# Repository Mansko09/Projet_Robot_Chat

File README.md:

# Projet Robot Chat

**ESE – Projet de groupe**

## Introduction

Dans le cadre de la spécialité de 3e année ESE à l'ENSEA, ce projet a pour objectif la conception complète d’un **robot mobile autonome à deux roues motrices**, destiné à participer à un jeu de type **chat et souris** face aux robots des autres groupes. Ce projet a été réalisé par Florian, David, Danilo et Mantou.
Au-delà de l’aspect ludique, ce projet mobilise des compétences variées en **électronique**, **mécanique** et **logiciel embarqué temps réel**, avec des contraintes fortes de sécurité (anti-chute), de réactivité et de robustesse matérielle.

Le robot, nommé **Félix**, doit être capable de se déplacer de manière autonome, de détecter son environnement, de réagir à des événements physiques (vide, chocs) et d’adapter dynamiquement son comportement.

---

## Objectifs fonctionnels

Pour atteindre ce comportement, plusieurs fonctions clés doivent être mises en place :

1. **Déplacement**

   * Roues + moteurs
   * Drivers de moteurs (PWM via timers)
   * Encodeurs (lecture via timers)

2. **Anti-chute**

   * Détection des bords avec capteur **ToF** (I²C)

3. **Détection des adversaires**

   * Capteur **LIDAR** pour repérer d’autres robots

4. **Détection de collisions**

   * Échange de rôles lors d’un choc (capteur **accéléromètre**)

5. **Communication**

   * Liaison **Bluetooth** (STM32WB55CEU6)

6. **Alimentation**

   * Batterie et gestion d’énergie (7.2 V → régulateurs 5 V & 3.3 V)

---

## Composants principaux

* **Microcontrôleur** : STM32WB55CEU6 (ARM Cortex-M4, BLE intégré)
* **Quartz** : 32 MHz 
* **Connecteur SWD/STLink** : (Farnell : 3226055)
* **Moteurs** : DFRobot FIT0520 ou FIT0521
* **Alimentation** : Batterie NiMH 7.2 V 1.3 Ah (RS : 777-0377)

  * Régulateur 5 V : MP1475DJ-LF-P
  * Régulateur 3.3 V : BU33SD5WG-TR
* **Drivers moteurs** : ZXBM5210 (un par roue)
* **Capteurs** :

  * LIDAR YDLIDAR X2
  * Accéléromètre ADXL343BCCZ-RL
  * Capteur ToF anti-chute
  * Multiplexeur : TCA9548A
* **Connecteurs** : JST 2.54 mm
* **Interface utilisateur** :

  * LED rouge/verte
  * Boutons poussoirs Wurth 430182070816 (6×6 mm, H9.5 mm)
  * Interrupteur ON/OFF Wurth 472121020311

---

## Conception réalisée

1. **Électronique**

   * Schéma électrique et PCB personnalisé
   * Routage, fabrication et soudure des composants

2. **Mécanique**

   * Conception du châssis sur **Onshape**
   * Intégration du PCB, moteurs, capteurs et batterie

3. **Logiciel embarqué**

   * Contrôle moteurs et capteurs

## Avancement du projet

* [x] Choix des composants et architecture générale
* [x] Schéma et routage PCB
* [x] Impression 3D du robot
* [x] Développement logiciel de base
* [ ] Intégration LIDAR et logique “chat/souris”

## Architecture générale 

## Structure du Code

### 1. Cerveau et Communication

Nous avons retenu le microcontrôleur **STM32WB55CEU6**, un choix motivé par des considérations de performance, de modularité et de fiabilité.

- **Mobilité et pilotage des drivers**  
  Chaque moteur est commandé par un driver piloté en PWM. Le logiciel intègre une gestion avancée des rampes de vitesse avec des profils asymétriques : accélération progressive et freinage brutal. Cette approche permet de préserver les moteurs tout en assurant un arrêt d’urgence immédiat lors de la détection de vide.  
  Les modes de freinage exploitent le **BRAKE_MODE** (court-circuit des moteurs) via le pont en H afin de garantir une immobilisation quasi instantanée sur les bords de table.

- **Intelligence embarquée et navigation**  
  Grâce à l’odométrie différentielle et aux encodeurs, la position $(x, y)$ ainsi que l’orientation $(\theta)$ du robot sont calculées en temps réel, permettant une navigation autonome précise.

- **Architecture logicielle sous FreeRTOS**  
  Le logiciel est structuré autour de plusieurs tâches concurrentes :
  - **Task_TOF** : mise à jour de la variable `vide` toutes les 20 ms, indiquant l’identifiant du capteur ToF détectant un vide ;
  - **Task_Motor** : gestion de l’odométrie et application des signaux PWM toutes les 10 ms ;
  - **Task_Control** : tâche décisionnelle principale, exécutée toutes les 20 ms, implémentant une machine à états finis (FSM) pilotant le comportement global du robot.

  **Rôle détaillé de la Task_Control**  
  La tâche **Task_Control** agit comme le véritable « cerveau » du robot. Elle fonctionne de manière asynchrone par rapport à la commande des moteurs et s’appuie sur une **Machine à États Finis (FSM)** pour orchestrer les actions de Félix en fonction des événements extérieurs.

  1. **Gestion de l’état global (Start / Stop)**  
     Avant toute logique de déplacement, la tâche surveille le flag `AccData`, mis à jour par l’accéléromètre via une interruption matérielle.  
     Un choc détecté agit comme un interrupteur logiciel (*toggle*) :
     - passage à l’état **Inactif** : LED rouge allumée, moteurs coupés ;
     - passage à l’état **Actif** : LED verte allumée, lancement de la mission.

  2. **Séquençage des déplacements (FSM)**  
     Lorsque le robot est actif, il suit un cycle comportemental conçu pour la survie et l’exploration :
     - **MOVE_FWD (marche avant)** : état par défaut. La tâche surveille en continu le registre `vide`. Dès qu’une bordure est détectée par un capteur ToF, une transition immédiate vers l’état de freinage est imposée.
     - **MOVE_BRAKE (sécurité)** : état intermédiaire déclenchant un arrêt d’urgence, voire une brève impulsion inverse, afin de compenser l’inertie et empêcher le dépassement du bord.
     - **MOVE_BACKWARD & MOVE_TURN** : une fois le robot immobilisé, une manœuvre de dégagement est engagée. Celle-ci est temporisée par `timer_state` et permet au robot de reculer, de modifier son orientation, puis de revenir automatiquement à l’état **MOVE_FWD**.

- **Perception sensorielle anti-chute**  
  Quatre capteurs **ToF VL53L0X** surveillent en permanence les angles du robot afin de détecter la présence de vide.

- **Détection de choc**  
  L’accéléromètre **ADXL343** est configuré en mode *Single Tap*. Un choc mécanique déclenche une interruption matérielle (EXTI) provoquant l’arrêt immédiat du robot et l’allumage de la LED rouge. Un second choc relance le système et active la LED verte.

## Ce qui fonctionne

- Déplacement fluide à une vitesse donnée du robot
- Détection de vide par les capteurs **ToF**
- Détection de choc par l’**accéléromètre**
- Gestion des LED d’état
- Changement de comportement en fonction :
  - de la détection de vide ;
  - de la détection de choc (Start / Stop)
 
## Ce qui ne fonctionne pas / partiellement

- **Bluetooth** : dysfonctionnement lié à un problème de quartz, empêchant la communication BLE
- **LIDAR** : matériel fonctionnel, mais logique logicielle incomplète
- **Asservissement** : implémenté mais non testé

## Challenges techniques rencontrés

### 1. Routage du PCB
Le premier défi a été le routage de la carte électronique :
- placement optimal des composants dans un espace réduit ;
- maintien des condensateurs de découplage au plus près du microcontrôleur ;
- isolation stricte de l’antenne Bluetooth ;
- optimisation des plans de masse ;
- éviter toute structure pouvant agir comme une antenne parasite.

### 2. Programmation du comportement du robot
Coder le comportement de Félix a été un défi majeur, non pas par la complexité de chaque fonction, mais par la nécessité de synchroniser une **logique** avec des **contraintes physiques réelles**.

#### a. Gestion du temps réel (priorités FreeRTOS)
Le robot ne doit jamais tomber, même lorsqu’il exécute d’autres calculs.
- **Problème** : la lecture des ToF via I²C est lente, alors que les moteurs nécessitent des mises à jour très fréquentes.
- **Solution** : architecture préemptive avec une priorité plus élevée pour la tâche ToF. En cas de détection de bord, elle interrompt la logique de contrôle pour forcer l’arrêt immédiat.

#### b. Passage du “tout ou rien” aux rampes (inertie)
- **Problème** : arrêts trop brutaux/lents provoquant des contraintes mécaniques (robot trop lourd à l'avant) ou un arrêt avec une roue en dehors de la table.
- **Solution** : implémentation de rampes asymétriques dans `Motor_UpdateSpeed` :
  - accélération douce (100 unités) ;
  - freinage très rapide (1000 unités).

Ce compromis entre protection mécanique et réactivité a nécessité de nombreux réglages.

#### c. Machine à États
- **Problème** : risque de blocage dans des situations critiques (coin de table, détections multiples).
- **Solution** : FSM rigoureuse avec des conditions de sortie strictes pour chaque état  
  (MOVE_FWD, MOVE_BRAKE, MOVE_BACKWARD, MOVE_TURN), garantissant un comportement déterministe et robuste.

https://github.com/user-attachments/assets/55dbaec2-2ef9-4583-8b24-4435a5f01540

## Conclusion

Ce projet a permis de mettre en pratique l’ensemble de la chaîne de conception d’un système embarqué autonome, depuis le routage d’un PCB jusqu’à la programmation temps réel sous FreeRTOS.  
Malgré certaines fonctionnalités incomplètes (Bluetooth, LIDAR), le robot démontre un comportement fiable et sécurisé face aux événements critiques. Les défis rencontrés ont été formateurs et ont mis en évidence l’importance de l’architecture logicielle et des choix matériels en amont dans un système embarqué réel.

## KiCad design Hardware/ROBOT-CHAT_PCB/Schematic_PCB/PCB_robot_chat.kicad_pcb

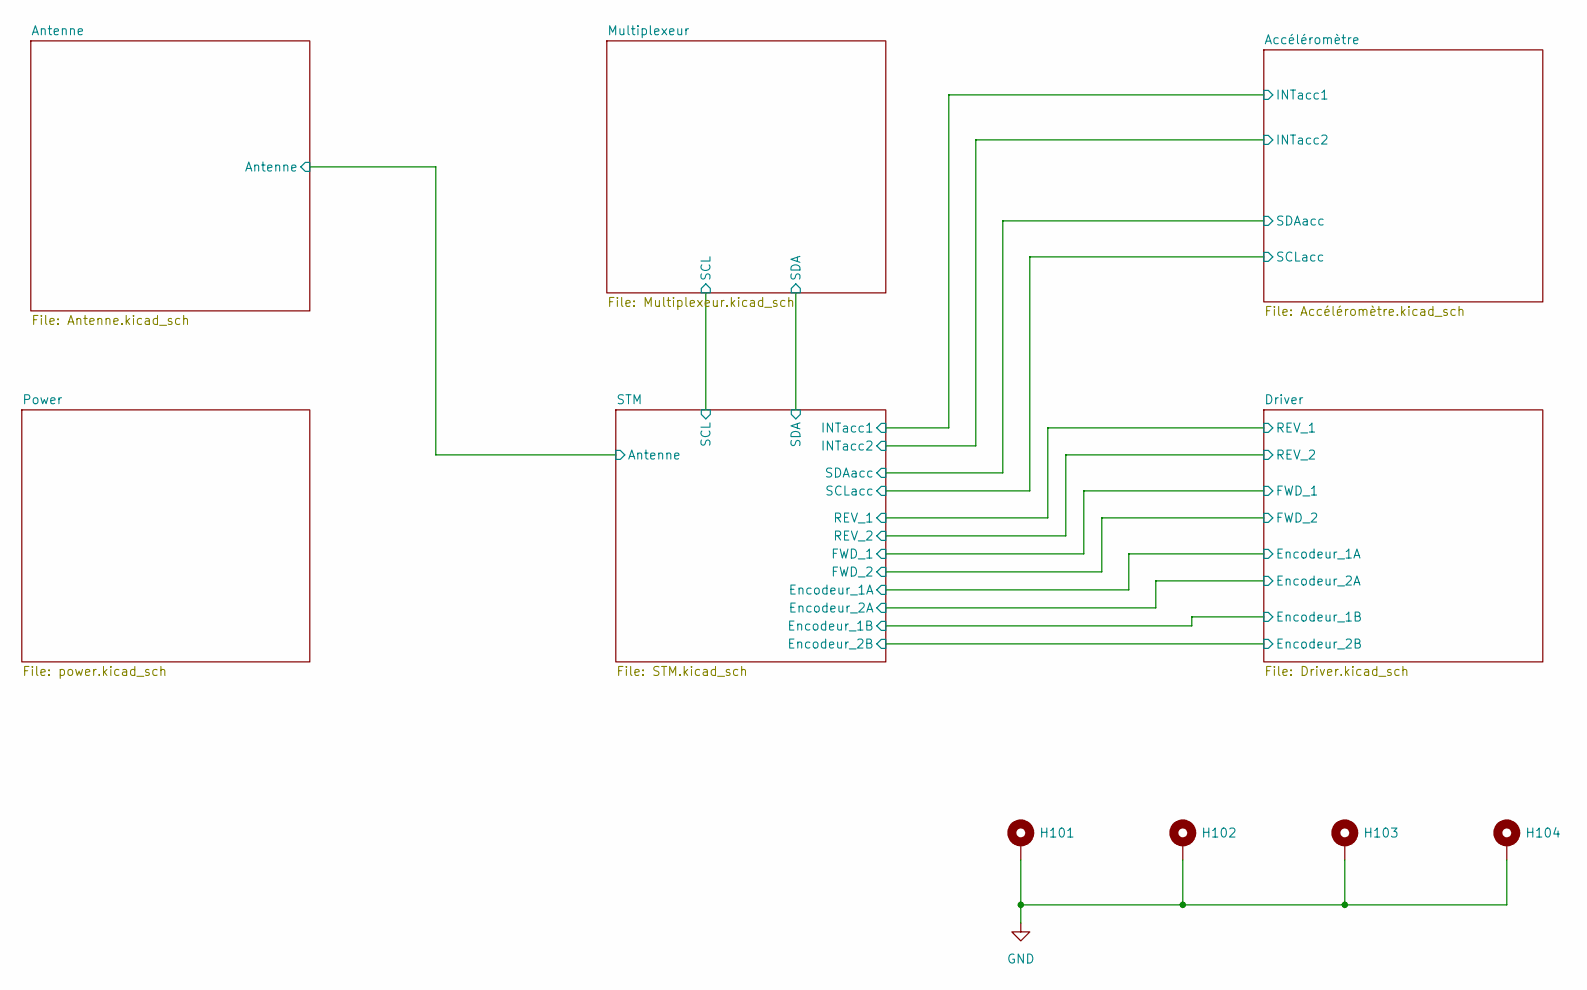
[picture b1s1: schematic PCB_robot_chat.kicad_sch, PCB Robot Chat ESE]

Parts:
H101, H102, H103, H104: MountingHole_Pad; MountingHole_2.5mm_Pad_Via

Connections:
GND: H101.1, H102.1, H103.1, H104.1; also elsewhere on the board

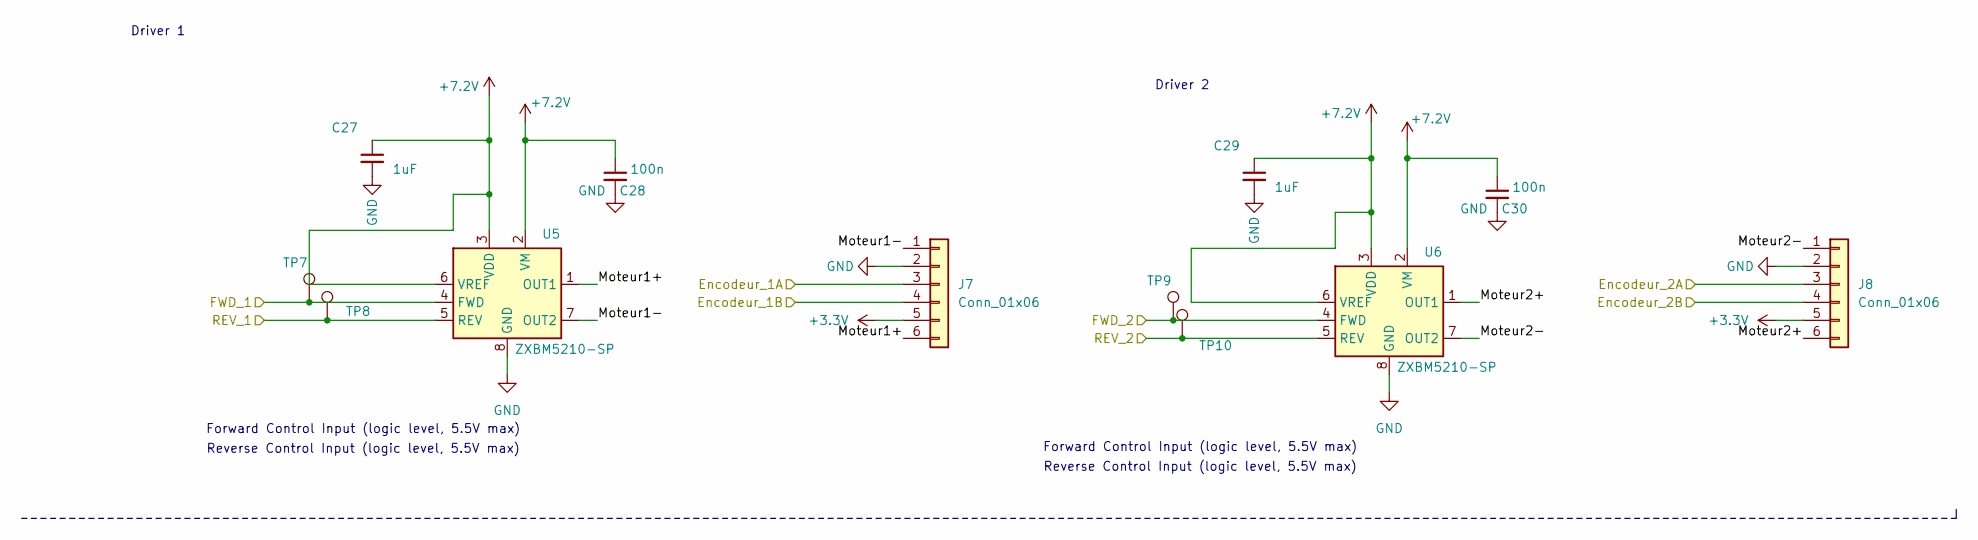
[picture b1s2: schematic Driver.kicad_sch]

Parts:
C27, C29: 1uF; C_0603_1608Metric
C28, C30: 100n; C_0402_1005Metric
J7, J8: Conn_01x06; JST_PH_B6B-PH-K_1x06_P2.00mm_Vertical
TP7, TP8, TP9, TP10: TestPoint; TestPoint_Pad_D1.5mm
U5, U6: ZXBM5210-SP; Diodes_SO-8EP

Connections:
+3.3V: J7.5, J8.5; also elsewhere on the board
+7.2V: C27.1, C28.1, C29.1, C30.1, U5.2 (VM), U5.3 (VDD), U5.6 (VREF), U6.2 (VM), U6.3 (VDD), U6.6 (VREF); also elsewhere on the board
/Driver/Encodeur_1A: J7.3; also elsewhere on the board
/Driver/Encodeur_1B: J7.4; also elsewhere on the board
/Driver/Encodeur_2A: J8.3; also elsewhere on the board
/Driver/Encodeur_2B: J8.4; also elsewhere on the board
/Driver/FWD_1: TP7.1, U5.4 (FWD); also elsewhere on the board
/Driver/FWD_2: TP9.1, U6.4 (FWD); also elsewhere on the board
/Driver/Moteur1+: J7.6, U5.1 (OUT1)
/Driver/Moteur1-: J7.1, U5.7 (OUT2)
/Driver/Moteur2+: J8.6, U6.1 (OUT1)
/Driver/Moteur2-: J8.1, U6.7 (OUT2)
/Driver/REV_1: TP8.1, U5.5 (REV); also elsewhere on the board
/Driver/REV_2: TP10.1, U6.5 (REV); also elsewhere on the board
GND: C27.2, C28.2, C29.2, C30.2, J7.2, J8.2, U5.8 (GND), U5.9 (GND), U6.8 (GND), U6.9 (GND); also elsewhere on the board

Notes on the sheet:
Forward Control Input (logic level, 5.5V max)
Driver 2
Reverse Control Input (logic level, 5.5V max)
Driver 1

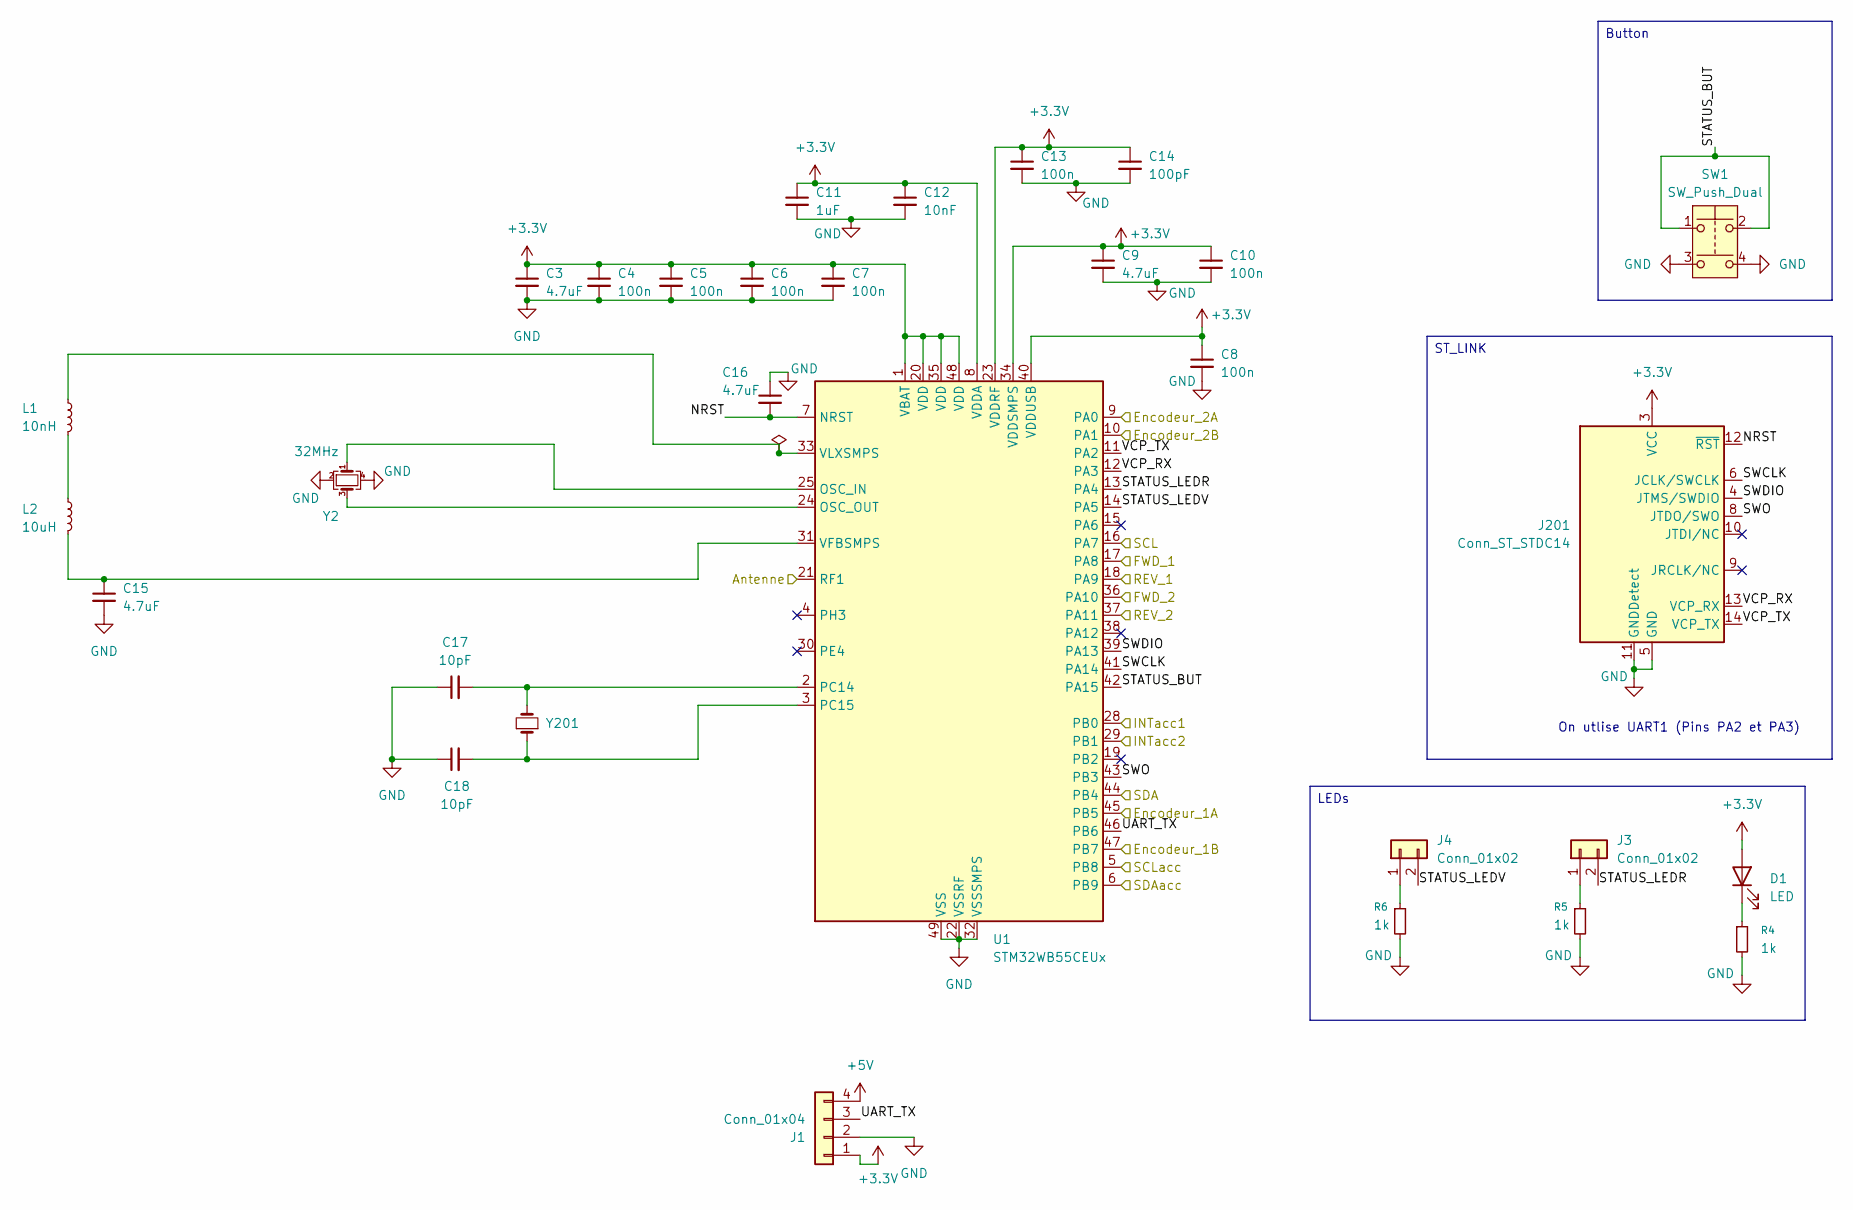
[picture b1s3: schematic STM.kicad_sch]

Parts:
C3, C9, C15, C16: 4.7uF; C_0603_1608Metric
C4, C5, C6, C7, C8, C10, C13: 100n; C_0402_1005Metric
C11: 1uF; C_0603_1608Metric
C12: 10nF; C_0402_1005Metric
C14: 100pF; C_0402_1005Metric
C17, C18: 10pF; C_0402_1005Metric
D1: LED; LED_0603_1608Metric
J1: Conn_01x04; JST_XH_B4B-XH-AM_1x04_P2.50mm_Vertical
J3, J4: Conn_01x02; JST_PH_B2B-PH-K_1x02_P2.00mm_Vertical
J201: Conn_ST_STDC14; PinHeader_2x07_P1.27mm_Vertical_SMD
L1: 10nH; L_0603_1608Metric
L2: 10uH; L_0603_1608Metric
R4, R5, R6: 1k; R_0402_1005Metric
SW1: SW_Push_Dual; SW_Push_1P1T_NO_6x6mm_H9.5mm
U1: STM32WB55CEUx; QFN-48-1EP_7x7mm_P0.5mm_EP5.6x5.6mm
Y2: 32MHz; XRCGB32M000F2P01R0
Y201: Crystal_Small; ABS07AIG-32.768KHZ-6-D-T

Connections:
+3.3V: C3.1, C4.1, C5.1, C6.1, C7.1, C8.1, C9.1, C10.1, C11.1, C12.1, C13.1, C14.1, D1.2 (A), J1.1, J201.3 (VCC), U1.1 (VBAT), U1.8 (VDDA), U1.20 (VDD), U1.23 (VDDRF), U1.34 (VDDSMPS), U1.35 (VDD), U1.40 (VDDUSB), U1.48 (VDD); also elsewhere on the board
+5V: J1.4; also elsewhere on the board
/Accéléromètre/INTacc1: U1.28 (PB0); also elsewhere on the board
/Accéléromètre/INTacc2: U1.29 (PB1); also elsewhere on the board
/Accéléromètre/SCLacc: U1.5 (PB8); also elsewhere on the board
/Accéléromètre/SDAacc: U1.6 (PB9); also elsewhere on the board
/Antenne/Antenne: U1.21 (RF1); also elsewhere on the board
/Driver/Encodeur_1A: U1.45 (PB5); also elsewhere on the board
/Driver/Encodeur_1B: U1.47 (PB7); also elsewhere on the board
/Driver/Encodeur_2A: U1.9 (PA0); also elsewhere on the board
/Driver/Encodeur_2B: U1.10 (PA1); also elsewhere on the board
/Driver/FWD_1: U1.17 (PA8); also elsewhere on the board
/Driver/FWD_2: U1.36 (PA10); also elsewhere on the board
/Driver/REV_1: U1.18 (PA9); also elsewhere on the board
/Driver/REV_2: U1.37 (PA11); also elsewhere on the board
/Multiplexeur/SCL: U1.16 (PA7); also elsewhere on the board
/Multiplexeur/SDA: U1.44 (PB4); also elsewhere on the board
/STM/NRST: C16.2, J201.12 (~RST), U1.7 (NRST)
/STM/STATUS_BUT: SW1.1, SW1.2, U1.42 (PA15)
/STM/STATUS_LEDR: J3.2, U1.13 (PA4)
/STM/STATUS_LEDV: J4.2, U1.14 (PA5)
/STM/SWCLK: J201.6 (JCLK/SWCLK), U1.41 (PA14)
/STM/SWDIO: J201.4 (JTMS/SWDIO), U1.39 (PA13)
/STM/SWO: J201.8 (JTDO/SWO), U1.43 (PB3)
/STM/UART_TX: J1.3, U1.46 (PB6)
/STM/VCP_RX: J201.13 (VCP_RX), U1.12 (PA3)
/STM/VCP_TX: J201.14 (VCP_TX), U1.11 (PA2)
GND: C3.2, C4.2, C5.2, C6.2, C7.2, C8.2, C9.2, C10.2, C11.2, C12.2, C13.2, C14.2, C15.2, C16.1, C17.1, C18.1, J1.2, J201.5 (GND), J201.7 (GND), J201.11 (GNDDetect), R4.2, R5.2, R6.2, SW1.3, SW1.4, U1.22 (VSSRF), U1.32 (VSSSMPS), U1.49 (VSS), Y2.2, Y2.4; also elsewhere on the board
unnamed: D1.1 (K), R4.1
unnamed: J3.1, R5.1
unnamed: J4.1, R6.1
unnamed: L1.2, L2.1
unnamed: U1.25 (OSC_IN), Y2.1
unnamed: U1.24 (OSC_OUT), Y2.3
unnamed: C17.2, U1.2 (PC14), Y201.2
unnamed: C18.2, U1.3 (PC15), Y201.1
unnamed: C15.1, L2.2, U1.31 (VFBSMPS)
unnamed: L1.1, U1.33 (VLXSMPS)

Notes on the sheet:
On utlise UART1 (Pins PA2 et PA3)
Button
ST_LINK
LEDs

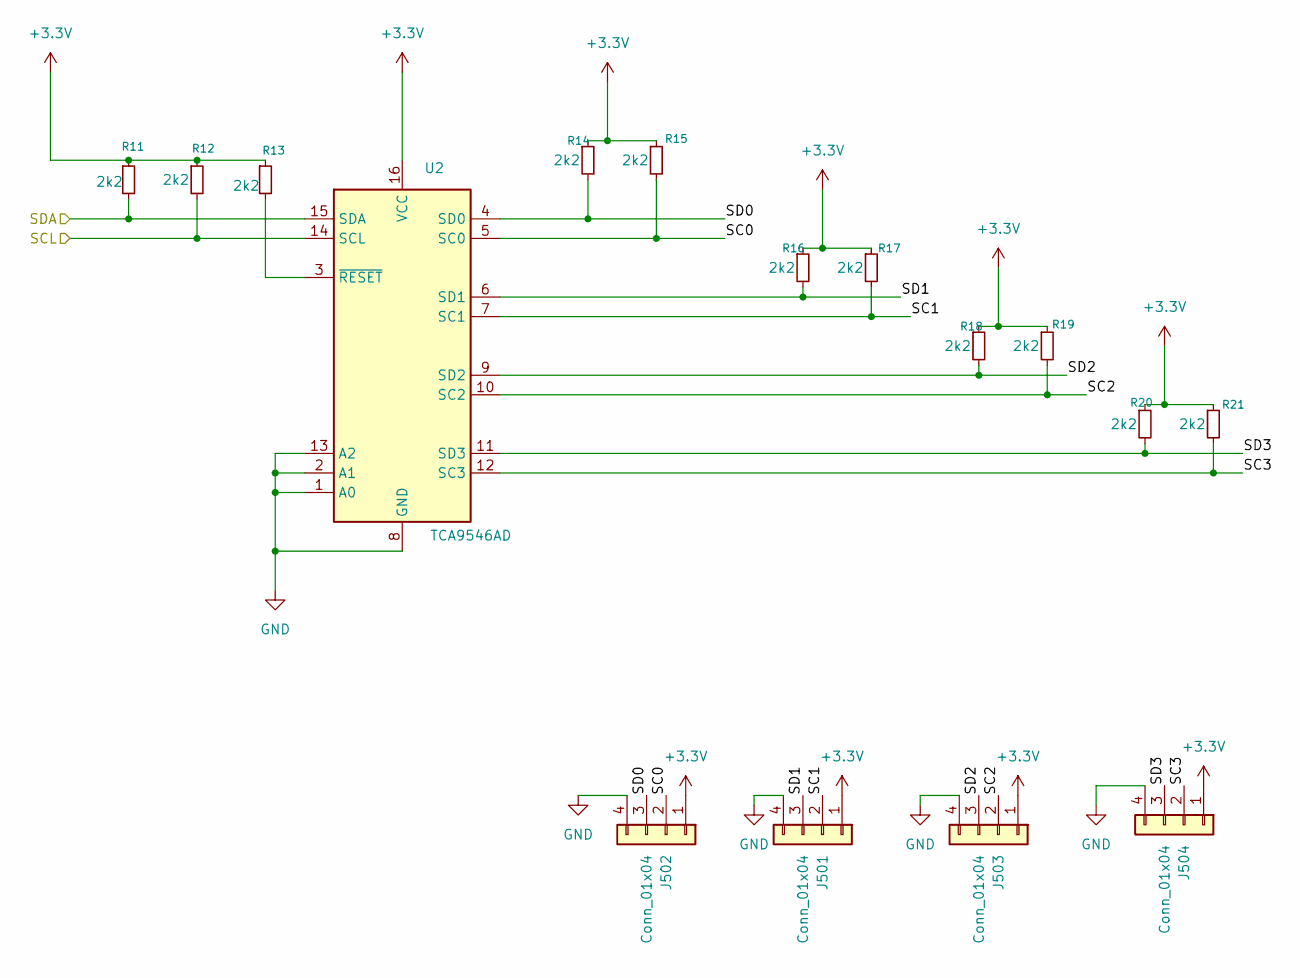
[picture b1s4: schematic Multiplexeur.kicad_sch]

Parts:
J501, J502, J503, J504: Conn_01x04; JST_PH_B4B-PH-K_1x04_P2.00mm_Vertical
R11, R12, R13, R14, R15, R16, R17, R18, R19, R20, R21: 2k2; R_0402_1005Metric
U2: TCA9546AD; SOIC-16_3.9x9.9mm_P1.27mm

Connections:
+3.3V: J501.1, J502.1, J503.1, J504.1, R11.1, R12.1, R13.1, R14.1, R15.1, R16.1, R17.1, R18.1, R19.1, R20.1, R21.1, U2.16 (VCC); also elsewhere on the board
/Multiplexeur/SC0: J502.2, R15.2, U2.5 (SC0)
/Multiplexeur/SC1: J501.2, R17.2, U2.7 (SC1)
/Multiplexeur/SC2: J503.2, R19.2, U2.10 (SC2)
/Multiplexeur/SC3: J504.2, R21.2, U2.12 (SC3)
/Multiplexeur/SCL: R12.2, U2.14 (SCL); also elsewhere on the board
/Multiplexeur/SD0: J502.3, R14.2, U2.4 (SD0)
/Multiplexeur/SD1: J501.3, R16.2, U2.6 (SD1)
/Multiplexeur/SD2: J503.3, R18.2, U2.9 (SD2)
/Multiplexeur/SD3: J504.3, R20.2, U2.11 (SD3)
/Multiplexeur/SDA: R11.2, U2.15 (SDA); also elsewhere on the board
GND: J501.4, J502.4, J503.4, J504.4, U2.1 (A0), U2.2 (A1), U2.8 (GND), U2.13 (A2); also elsewhere on the board
unnamed: R13.2, U2.3 (~RESET)

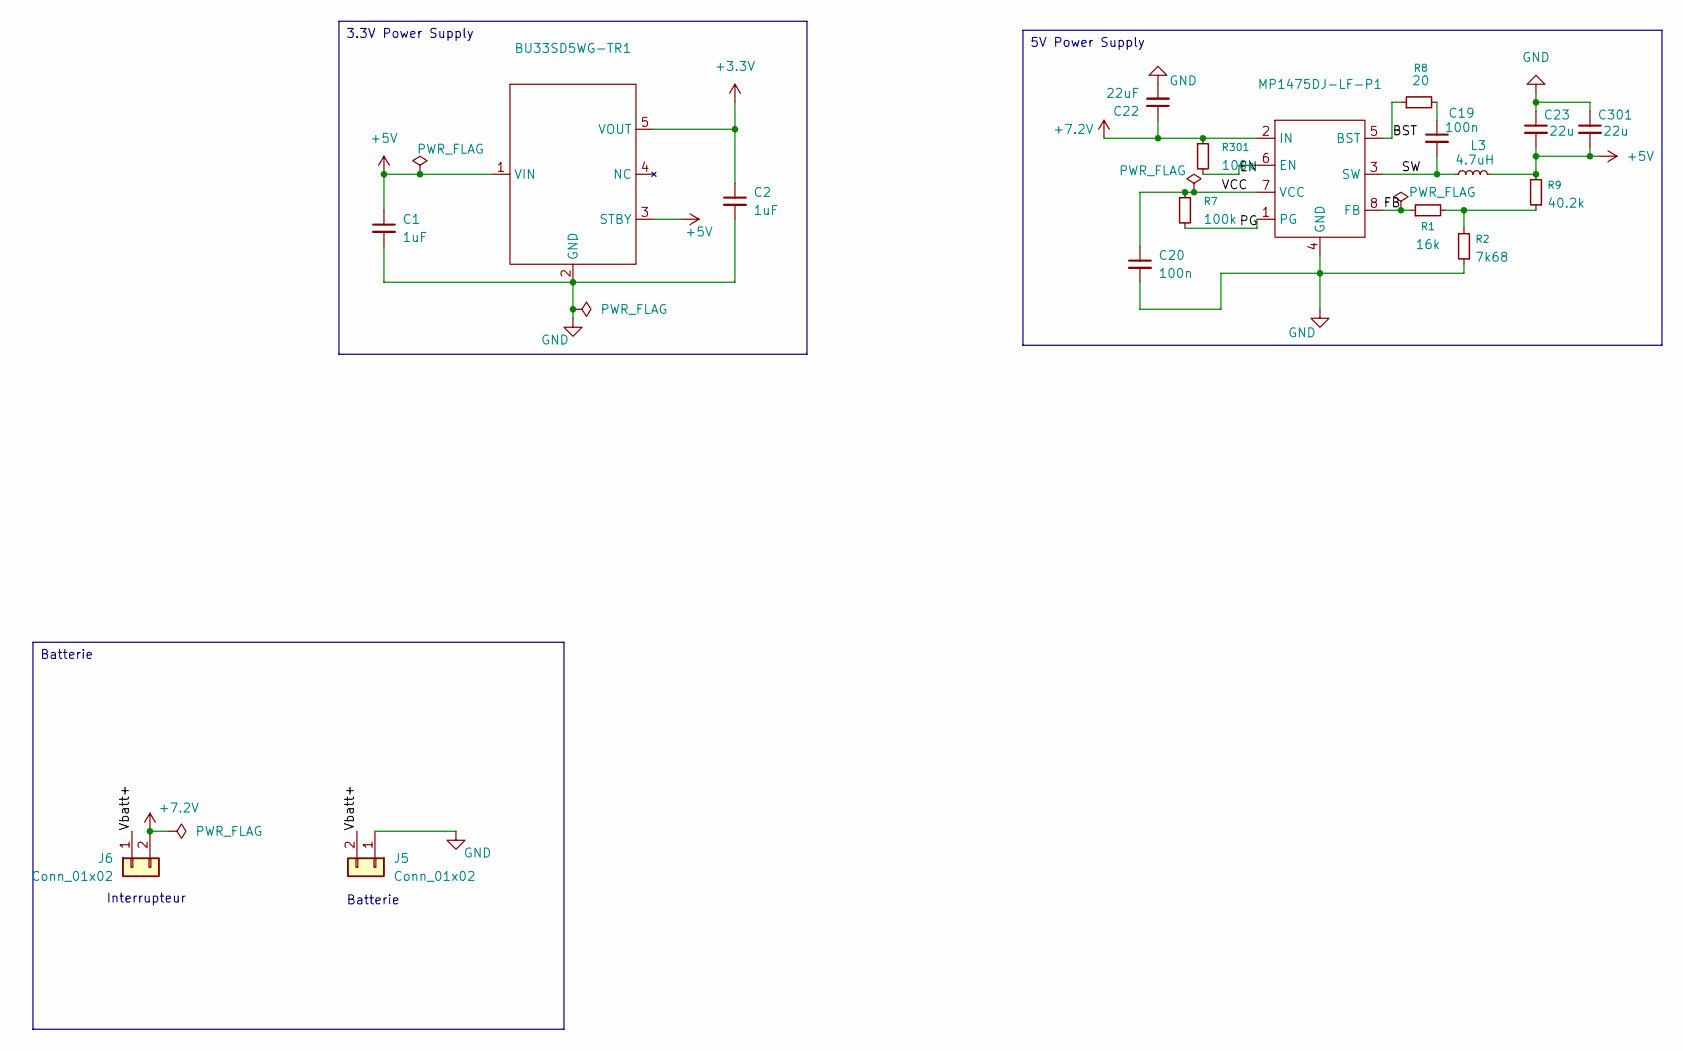
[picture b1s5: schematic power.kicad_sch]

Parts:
BU33SD5WG-TR1: SOT-23-5
C1, C2: 1uF; C_0603_1608Metric
C19, C20: 100n; C_0402_1005Metric
C22: 22uF; C_0805_2012Metric
C23, C301: 22u; C_0805_2012Metric
J5, J6: Conn_01x02; JST_PH_B2B-PH-K_1x02_P2.00mm_Vertical
L3: 4.7uH; Bobine_74404054068
MP1475DJ-LF-P1: TSOT-23-8
R1: 16k; R_0402_1005Metric
R2: 7k68; R_0402_1005Metric
R7, R301: 100k; R_0402_1005Metric
R8: 20; R_0402_1005Metric
R9: 40.2k; R_0402_1005Metric

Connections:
+3.3V: BU33SD5WG-TR1.5 (VOUT), C2.1; also elsewhere on the board
+5V: BU33SD5WG-TR1.1 (VIN), BU33SD5WG-TR1.3 (STBY), C1.1, C23.2, C301.2, L3.2, R9.2; also elsewhere on the board
+7.2V: C22.1, J6.2, MP1475DJ-LF-P1.2 (IN), R301.1; also elsewhere on the board
/Power/BST: MP1475DJ-LF-P1.5 (BST), R8.1
/Power/EN: MP1475DJ-LF-P1.6 (EN), R301.2
/Power/FB: MP1475DJ-LF-P1.8 (FB), R1.1
/Power/PG: MP1475DJ-LF-P1.1 (PG), R7.2
/Power/SW: C19.2, L3.1, MP1475DJ-LF-P1.3 (SW)
/Power/VCC: C20.1, MP1475DJ-LF-P1.7 (VCC), R7.1
/Power/Vbatt+: J5.2, J6.1
GND: BU33SD5WG-TR1.2 (GND), C1.2, C2.2, C20.2, C22.2, C23.1, C301.1, J5.1, MP1475DJ-LF-P1.4 (GND), R2.1; also elsewhere on the board
unnamed: C19.1, R8.2
unnamed: R1.2, R2.2, R9.1

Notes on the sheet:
Batterie
Interrupteur
3.3V Power Supply
5V Power Supply

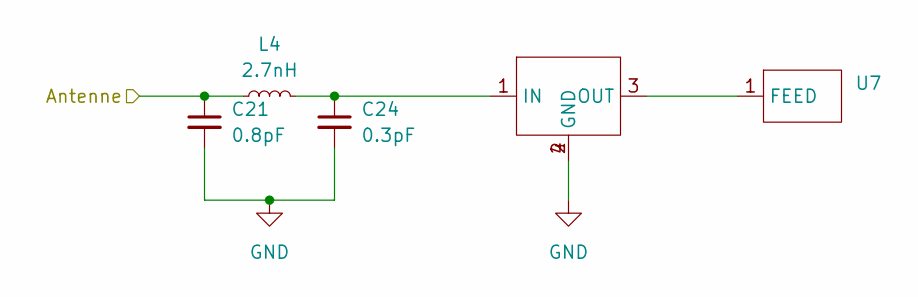
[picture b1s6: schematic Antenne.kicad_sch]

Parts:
C21: 0.8pF; C_0402_1005Metric
C24: 0.3pF; C_0402_1005Metric
L4: 2.7nH; L_0603_1608Metric
U7: AMCA31-2R450G-S1F-T3
U8: LOWPASS

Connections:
/Antenne/Antenne: C21.1, L4.1; also elsewhere on the board
GND: C21.2, C24.2, U8.2 (GND), U8.4 (GND); also elsewhere on the board
unnamed: U7.1 (FEED), U8.3 (OUT)
unnamed: C24.1, L4.2, U8.1 (IN)

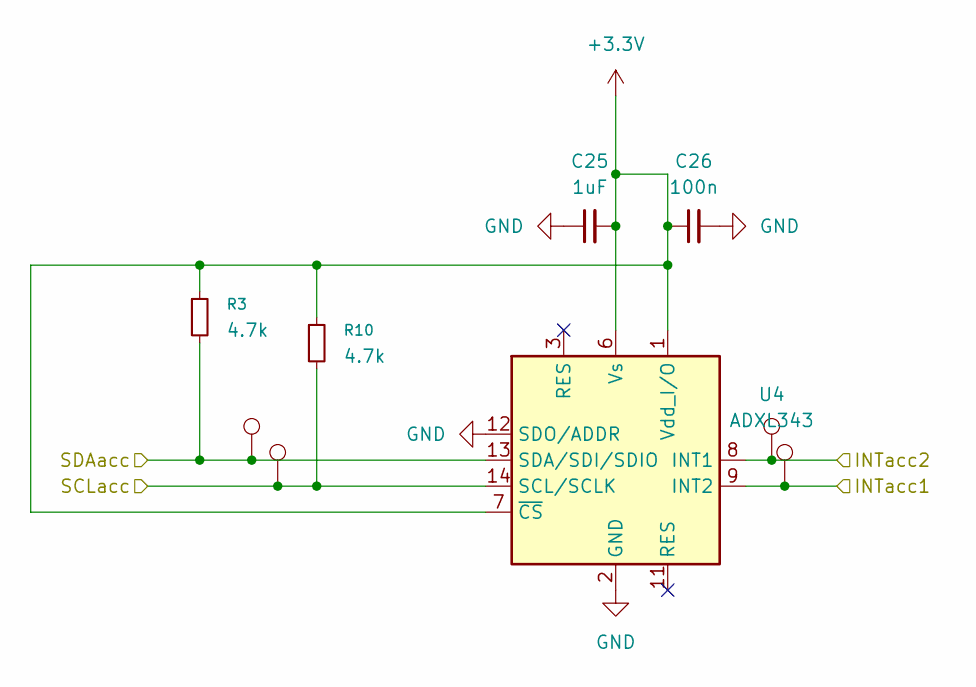
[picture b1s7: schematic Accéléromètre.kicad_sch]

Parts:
C25: 1uF; C_0603_1608Metric
C26: 100n; C_0402_1005Metric
R3, R10: 4.7k; R_0402_1005Metric
TP701, TP702, TP703, TP704: TestPoint; TestPoint_Pad_D1.5mm
U4: ADXL343; LGA-14_3x5mm_P0.8mm_LayoutBorder1x6y

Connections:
+3.3V: C25.2, C26.1, R3.1, R10.1, U4.1 (Vdd_I/O), U4.6 (Vs), U4.7 (~CS); also elsewhere on the board
/Accéléromètre/INTacc1: TP704.1, U4.9 (INT2); also elsewhere on the board
/Accéléromètre/INTacc2: TP703.1, U4.8 (INT1); also elsewhere on the board
/Accéléromètre/SCLacc: R10.2, TP702.1, U4.14 (SCL/SCLK); also elsewhere on the board
/Accéléromètre/SDAacc: R3.2, TP701.1, U4.13 (SDA/SDI/SDIO); also elsewhere on the board
GND: C25.1, C26.2, U4.2 (GND), U4.4 (GND), U4.5 (GND), U4.12 (SDO/ADDR); also elsewhere on the board

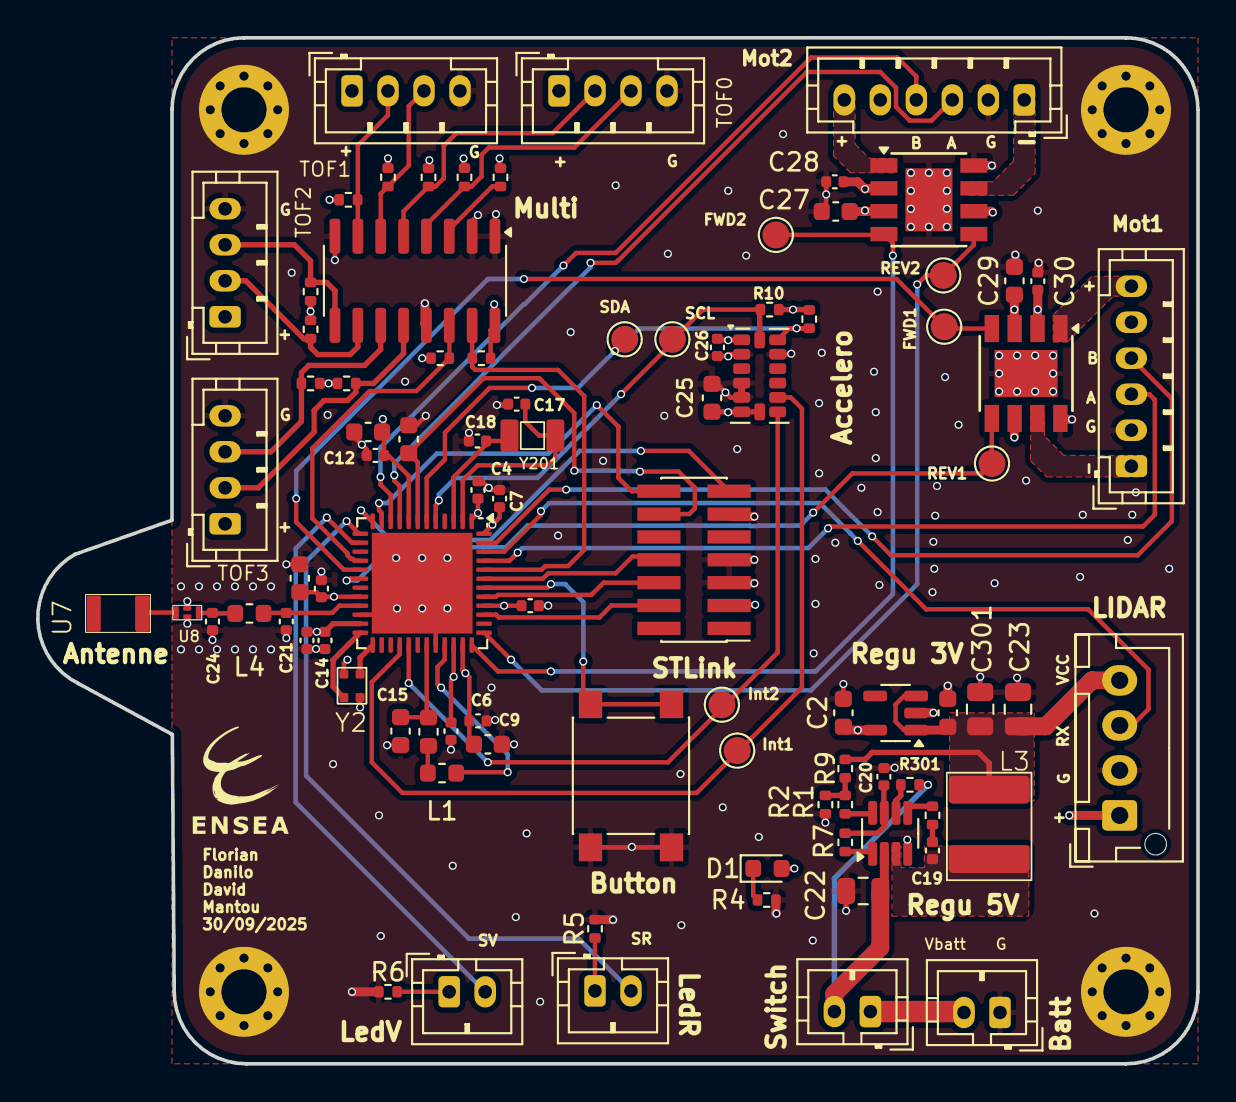
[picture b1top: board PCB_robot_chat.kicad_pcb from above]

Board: 4 copper layers, 64.5 x 57.0 mm, 94 parts (0 on the bottom side), 63 nets.

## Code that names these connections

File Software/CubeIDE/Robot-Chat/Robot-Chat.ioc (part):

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Mcu.Name=STM32WB55CEUx
Mcu.Package=UFQFPN48
Mcu.UserName=STM32WB55CEUx
PA0.GPIOParameters=GPIO_Label
PA0.GPIO_Label=Enc2A
PA0.Signal=S_TIM2_CH1
PA1.GPIOParameters=GPIO_Label
PA1.GPIO_Label=Enc2B
PA1.Signal=S_TIM2_CH2
PA10.GPIOParameters=GPIO_Label
PA10.GPIO_Label=M2_FWD
PA10.Signal=S_TIM1_CH3
PA11.GPIOParameters=GPIO_Label
PA11.GPIO_Label=M2_REV
PA11.Signal=S_TIM1_CH4
PA13.Mode=Trace_Asynchronous_SW
PA13.Signal=SYS_JTMS-SWDIO
PA14.Mode=Trace_Asynchronous_SW
PA14.Signal=SYS_JTCK-SWCLK
PA2.Mode=Asynchronous
PA2.Signal=LPUART1_TX
PA3.Mode=Asynchronous
PA3.Signal=LPUART1_RX
PA4.GPIOParameters=GPIO_Label
PA4.GPIO_Label=LED_ROUGE
PA4.Signal=GPIO_Output
PA5.GPIOParameters=GPIO_Label
PA5.GPIO_Label=LED_VERTE
PA5.Signal=GPIO_Output
PA7.Mode=I2C
PA7.Signal=I2C3_SCL
PA8.GPIOParameters=GPIO_Label
PA8.GPIO_Label=M1_FWD
PA8.Signal=S_TIM1_CH1
PA9.GPIOParameters=GPIO_Label
PA9.GPIO_Label=M1_REV
PA9.Signal=S_TIM1_CH2
PB0.GPIOParameters=GPIO_PuPd
PB0.GPIO_PuPd=GPIO_PULLDOWN
PB0.Signal=GPXTI0
PB1.GPIOParameters=GPIO_PuPd
PB1.GPIO_PuPd=GPIO_PULLDOWN
PB1.Signal=GPXTI1
PB3.Mode=Trace_Asynchronous_SW
PB3.Signal=SYS_JTDO-SWO
PB4.Mode=I2C
PB4.Signal=I2C3_SDA
PB5.Mode=Encoder_mode_occur1
PB5.Signal=LPTIM1_IN1
PB6.Mode=Half_duplex(single_wire_mode)
PB6.Signal=USART1_TX
PB7.Mode=Encoder_mode_occur1
PB7.Signal=LPTIM1_IN2
PB8.Mode=I2C
PB8.Signal=I2C1_SCL
PB9.Mode=I2C
PB9.Signal=I2C1_SDA
RCC.HSE_VALUE=32000000
RCC.SYSCLKFreq_VALUE=64000000
RCC.SYSCLKSource=RCC_SYSCLKSOURCE_PLLCLK
board=custom

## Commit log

2025-09-15 Added datasheets
2025-09-16 Ajout architecture générale et datasheet moteur
2025-09-16 MAJ architecture
2025-09-18 PCB - Ajout schématique driver
2025-09-19 PCB - Updated Driver schematic
2025-09-19 push Kicad DAVID
    j'espere que ca marche lol
2025-09-19 Ajout datasheet multiplexeur
2025-09-19 Rajout empreintes/Symbol antenna et passe-bas
2025-09-23 Ajout Schématique Finale
2025-09-26 current schematic
2025-09-29 Rerouting avec Mr Fiack
2025-09-30 Routage terminée, début serigraphie
2025-09-30 Sérigraphie terminée, PCB v2
2025-09-30 Ajout testpoint, PCB v3
2025-09-30 ajout librairies
2025-10-01 Fixed error pins timers, PCB version 4
2025-10-01 Created stm32CubeIDE project and initalized it
2025-10-01 Pins configuration changed
2025-10-01 Modif PCB after pin update, PCB version 5
2025-10-01 Verif by Fiack, PCB version 6
2025-10-01 PCB final version
2025-10-01 ajout de librairies I2C
2025-10-01 Modified pin M_control for the Lidar, PCV version 7
2025-10-01 adding tof api
2025-11-14 Updating pinout
2025-11-14 added BOM
2025-11-14 Deleted antenna space btw signals and change R2 value
2025-11-14 added pinout document
2025-11-19 Test motors ok
2025-11-25 Rename Moteurs to Moteurs.md
2025-11-26 Enabled EXT1 for Acc
2025-11-26 Create Meca folder
2025-11-26 Updated read me and architecture schema
2025-11-26 deleted old architecture schema
2025-11-26 Updated read me
2025-11-26 Created motors task
2025-11-26 Added task handle
2025-12-02 Test 2 motors ok + tasks creation
2025-12-03 adding TOF control
2025-12-03 Add code structure section to README
    Added code structure section with an image.
2025-12-03 Test moteurs enlevé
2025-12-10 tests tâches moteurs et odometrie
2026-01-02 reglage accélérometre
2026-01-02 test asservissement
2026-01-02 prepare to merge
2026-01-09 Tache control updated
2026-01-09 Tache control et tof fonctionnels
2026-01-09 Changes behavior with TOFs
2026-01-13 Tests detection vide robot
2026-01-14 Logique Tofs presque ok
2026-01-14 Meca update
2026-01-15 Un seul semaphore
2026-01-15 Keep Core changes; ignore generated files and backups
2026-01-15 [ACC] choc demarrage et stop
2026-01-15 Version beta ok (sans lidar)
2026-01-15 Ignore CubeIDE generated files (stop tracking .metadata/Debug/.settings)
2026-01-15 ajout des user_labels
2026-01-16 Version 1 ok avec leds
2026-01-17 last modification
2026-01-17 Revise README with updated project details
    Updated the README to reflect changes in components, architecture, and project status.
2026-01-17 Update README with new structure du code
2026-01-17 Enhance README with Task_Control details
    Detailed the role of Task_Control in the robot's operation, including state management and movement sequencing.
2026-01-17 cleaning and commenting
2026-01-17 Revise README with project introduction and status
    Updated project details, objectives, and challenges in README.
2026-01-17 Update README with problem and solution clarifications
    Clarified problems with abrupt stops and added details about mechanical constraints.
2026-01-17 Update README with video of robot
    Added a link to project assets and expanded the conclusion section.
2026-01-26 Add LIDAR sensor driver files
